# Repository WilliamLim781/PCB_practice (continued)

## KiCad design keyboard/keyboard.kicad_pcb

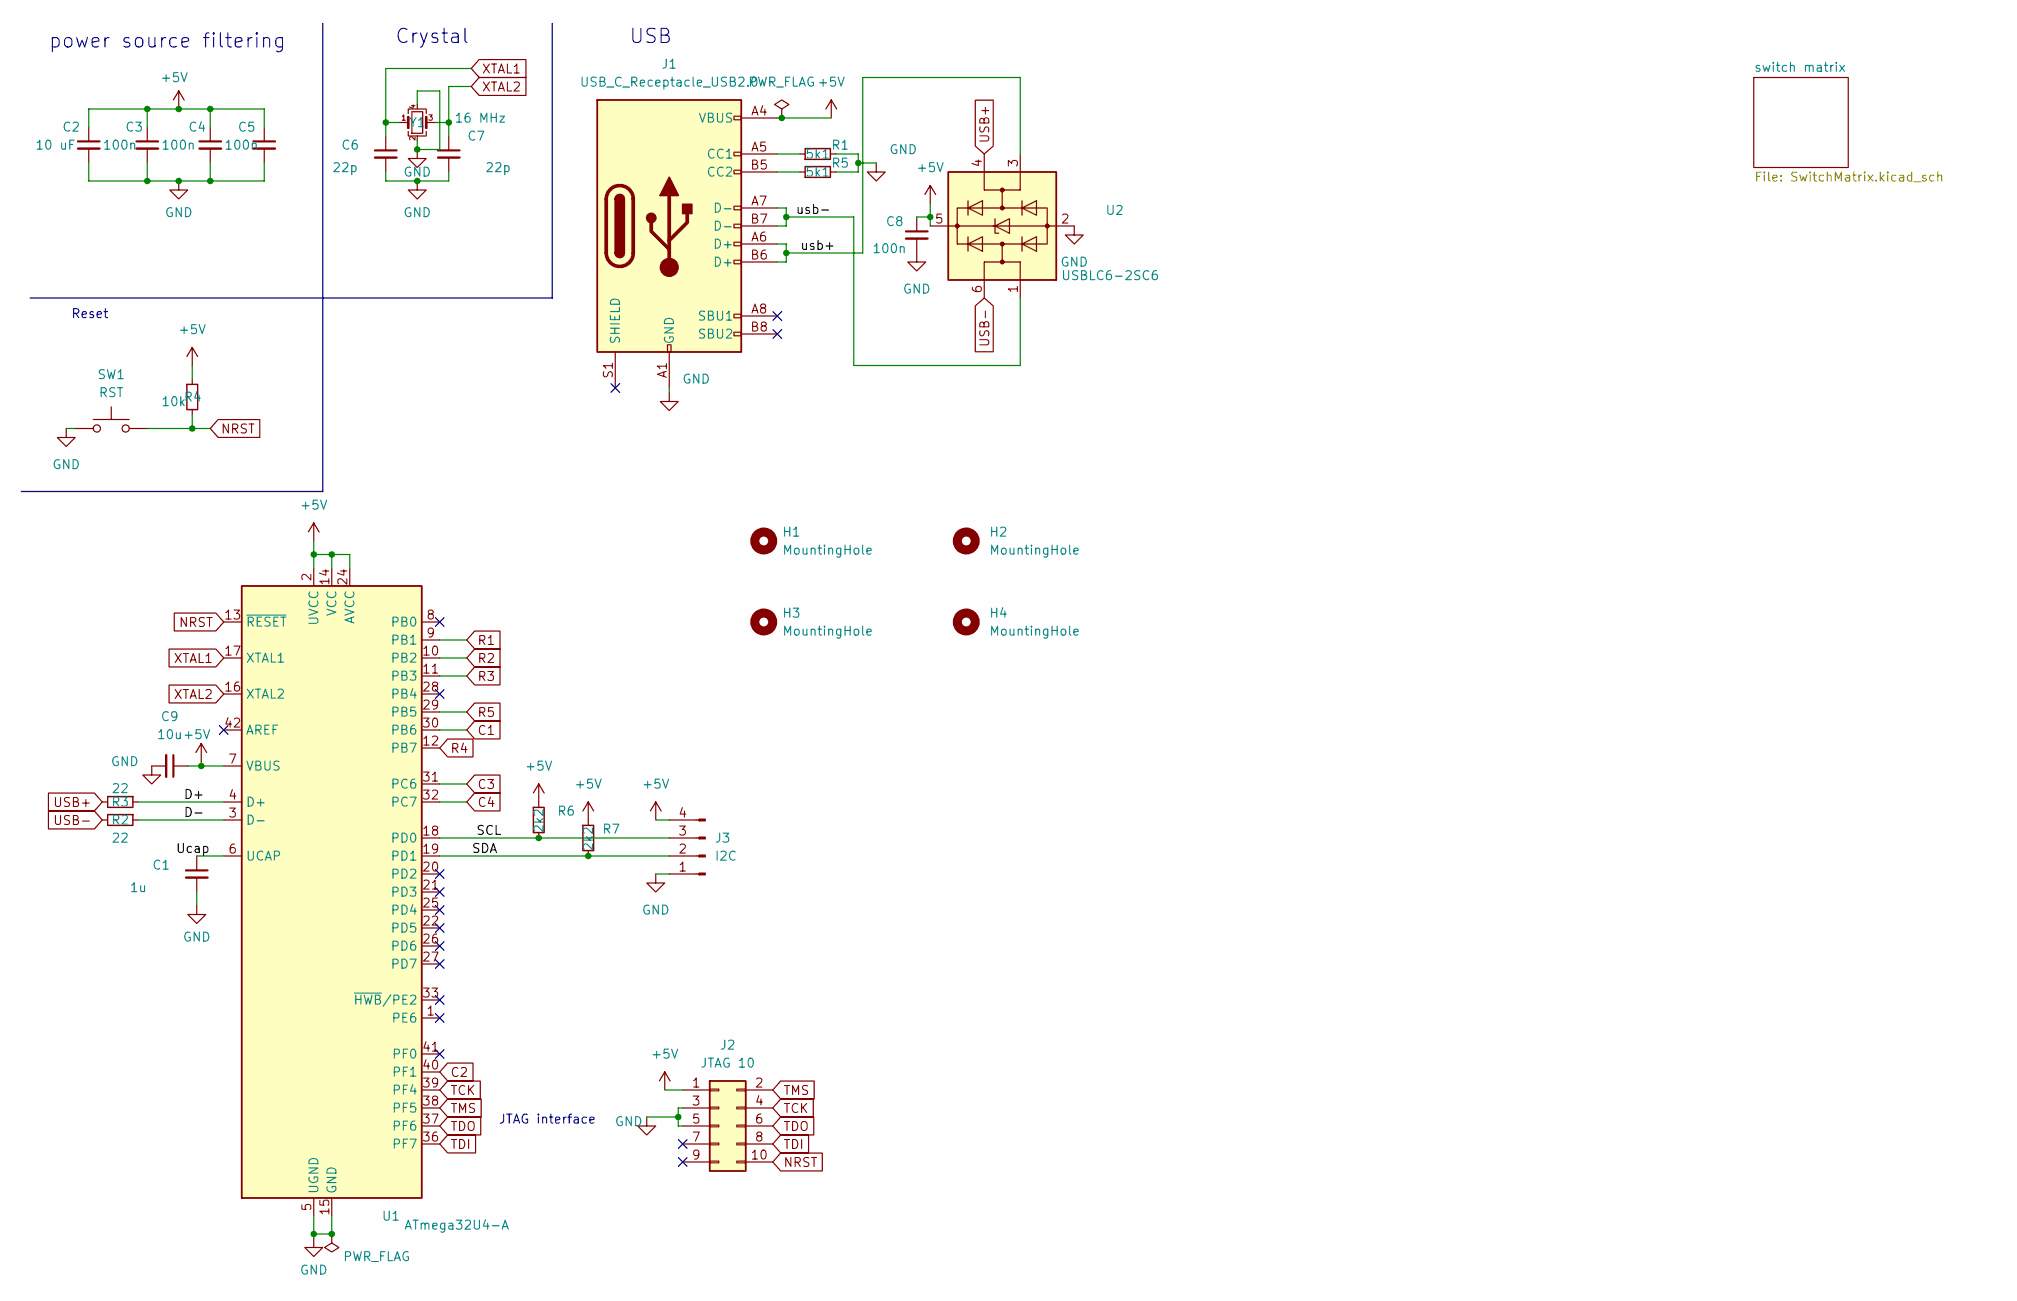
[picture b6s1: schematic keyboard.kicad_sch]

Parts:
C1: 1u; C_0603_1608Metric_Pad1.08x0.95mm_HandSolder
C2: 10 uF; C_0603_1608Metric_Pad1.08x0.95mm_HandSolder
C3, C4, C5, C8: 100n; C_0603_1608Metric_Pad1.08x0.95mm_HandSolder
C6, C7: 22p; C_0603_1608Metric_Pad1.08x0.95mm_HandSolder
C9: 10u; C_0603_1608Metric_Pad1.08x0.95mm_HandSolder
H1, H2, H3, H4: MountingHole; MountingHole_4.3mm_M4
J1: USB_C_Receptacle_USB2.0; USB_C_Receptacle_GCT_USB4105-xx-A_16P_TopMnt_Horizontal
J2: JTAG 10; PinHeader_2x05_P2.54mm_Vertical
J3: I2C; PinHeader_1x04_P2.54mm_Vertical
R1, R5: 5k1; R_0603_1608Metric_Pad0.98x0.95mm_HandSolder
R2, R3: 22; R_0603_1608Metric_Pad0.98x0.95mm_HandSolder
R4: 10k; R_0603_1608Metric_Pad0.98x0.95mm_HandSolder
R6, R7: 2k2; R_0603_1608Metric_Pad0.98x0.95mm_HandSolder
SW1: RST; SW_SPST_PTS645
U1: ATmega32U4-A; TQFP-44_10x10mm_P0.8mm
U2: USBLC6-2SC6; SOT-23-6
Y1: 16 MHz; Crystal_SMD_3225-4Pin_3.2x2.5mm_HandSoldering

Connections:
+5V: C2.1, C3.1, C4.1, C5.1, C8.1, C9.1, J1.A4 (VBUS), J1.A9 (VBUS), J1.B4 (VBUS), J1.B9 (VBUS), J2.1, J3.4, R4.1, R6.1, R7.1, U1.2 (UVCC), U1.7 (VBUS), U1.14 (VCC), U1.24 (AVCC), U1.34 (VCC), U1.44 (AVCC), U2.5 (VBUS)
/D+: R3.1, U1.4 (D+)
/D-: R2.1, U1.3 (D-)
/SCL: J3.3, R6.2, U1.18 (PD0)
/SDA: J3.2, R7.2, U1.19 (PD1)
/Ucap: C1.1, U1.6 (UCAP)
/usb+: J1.A6 (D+), J1.B6 (D+), U2.3 (I/O2)
/usb-: J1.A7 (D-), J1.B7 (D-), U2.1 (I/O1)
C1: U1.30 (PB6); also elsewhere on the board
C2: U1.40 (PF1); also elsewhere on the board
C3: U1.31 (PC6); also elsewhere on the board
C4: U1.32 (PC7); also elsewhere on the board
GND: C1.2, C2.2, C3.2, C4.2, C5.2, C6.2, C7.2, C8.2, C9.2, J1.A1 (GND), J1.A12 (GND), J1.B1 (GND), J1.B12 (GND), J2.3, J2.5, J3.1, R1.2, R5.2, SW1.1, U1.5 (UGND), U1.15 (GND), U1.23 (GND), U1.35 (GND), U1.43 (GND), U2.2 (GND), Y1.2, Y1.4
NRST: J2.10, R4.2, SW1.2, U1.13 (~RESET)
unnamed: J1.A5 (CC1), R1.1
unnamed: J1.B5 (CC2), R5.1
R1: U1.9 (PB1); also elsewhere on the board
R2: U1.10 (PB2); also elsewhere on the board
R3: U1.11 (PB3); also elsewhere on the board
R4: U1.12 (PB7); also elsewhere on the board
R5: U1.29 (PB5); also elsewhere on the board
TCK: J2.4, U1.39 (PF4)
TDI: J2.8, U1.36 (PF7)
TDO: J2.6, U1.37 (PF6)
TMS: J2.2, U1.38 (PF5)
USB+: R3.2, U2.4 (I/O2)
USB-: R2.2, U2.6 (I/O1)
XTAL1: C6.1, U1.17 (XTAL1), Y1.1
XTAL2: C7.1, U1.16 (XTAL2), Y1.3

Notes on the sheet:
Reset
Crystal
JTAG interface
power source filtering
USB

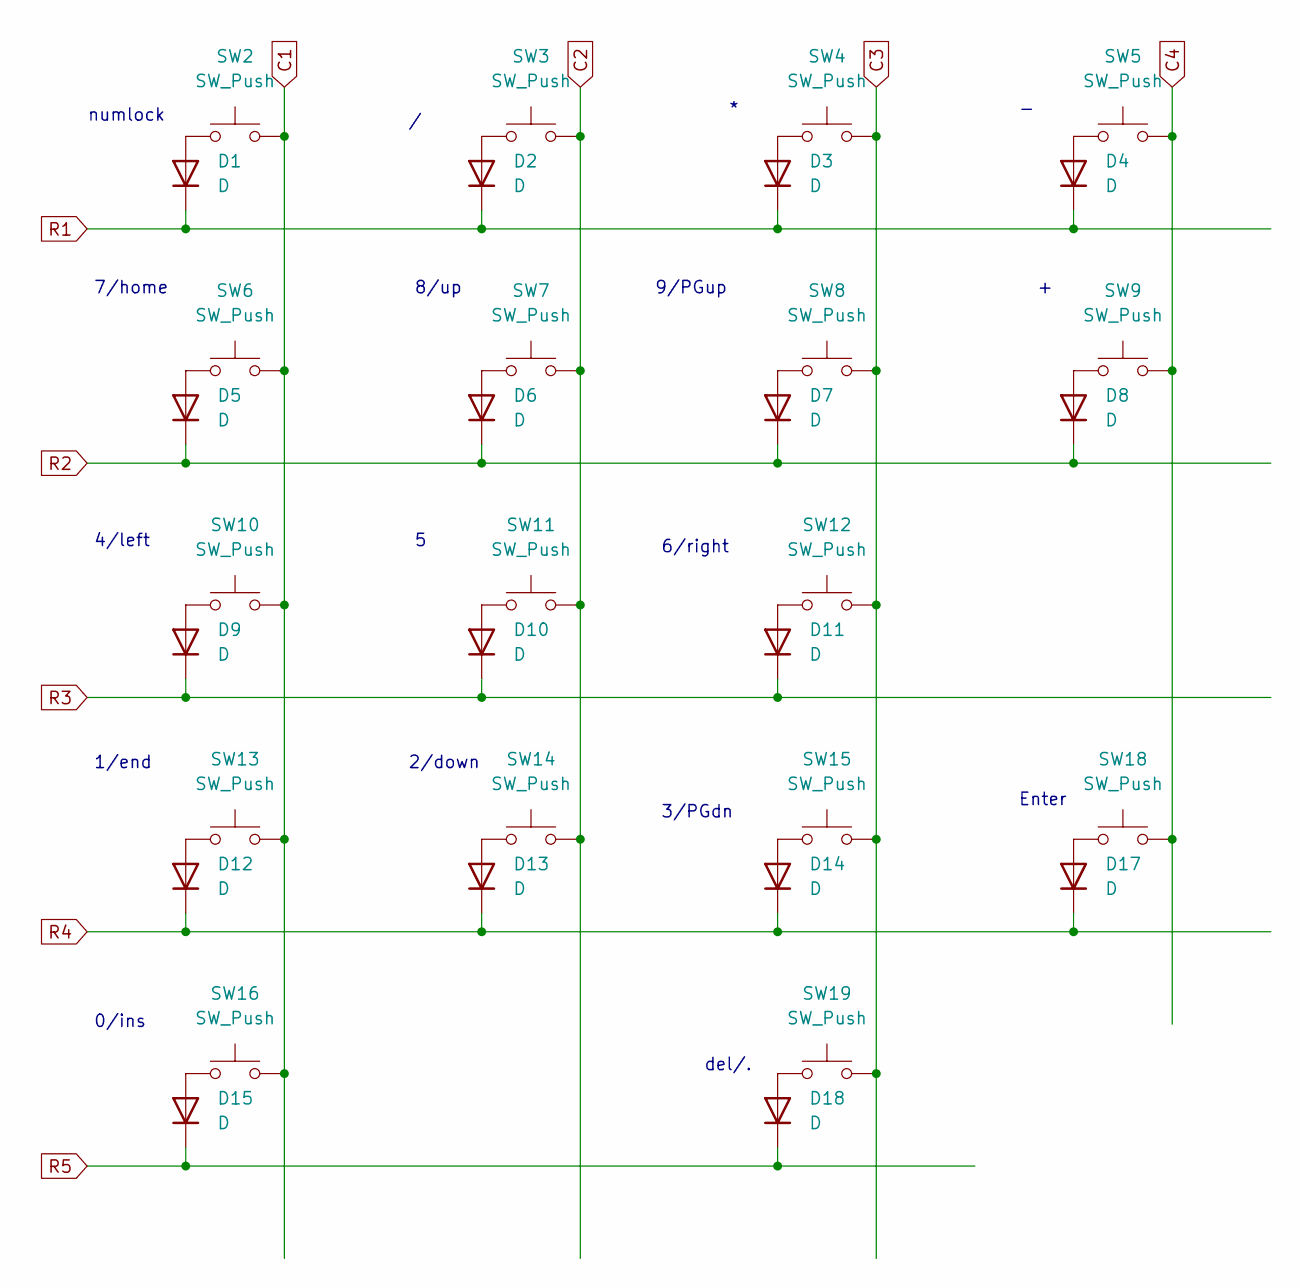
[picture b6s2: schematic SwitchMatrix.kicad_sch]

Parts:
D1, D2, D3, D4, D5, D6, D7, D8, D9, D10, D11, D12, D13, D14, D15, D17, D18: D; D_0603_1608Metric_Pad1.05x0.95mm_HandSolder
SW2, SW3, SW4, SW5, SW6, SW7, SW8, SW10, SW11, SW12, SW13, SW14, SW15, SW19: SW_Push; SW_Hotswap_Kailh_MX_1.00u
SW9, SW18: SW_Push; SW_Hotswap_Kailh_MX_2.00u_90deg
SW16: SW_Push; SW_Hotswap_Kailh_MX_2.00u

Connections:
C1: SW2.2, SW6.2, SW10.2, SW13.2, SW16.2; also elsewhere on the board
C2: SW3.2, SW7.2, SW11.2, SW14.2; also elsewhere on the board
C3: SW4.2, SW8.2, SW12.2, SW15.2, SW19.2; also elsewhere on the board
C4: SW5.2, SW9.2, SW18.2; also elsewhere on the board
unnamed: D1.2 (A), SW2.1
unnamed: D2.2 (A), SW3.1
unnamed: D3.2 (A), SW4.1
unnamed: D4.2 (A), SW5.1
unnamed: D5.2 (A), SW6.1
unnamed: D6.2 (A), SW7.1
unnamed: D7.2 (A), SW8.1
unnamed: D8.2 (A), SW9.1
unnamed: D9.2 (A), SW10.1
unnamed: D10.2 (A), SW11.1
unnamed: D11.2 (A), SW12.1
unnamed: D12.2 (A), SW13.1
unnamed: D13.2 (A), SW14.1
unnamed: D14.2 (A), SW15.1
unnamed: D15.2 (A), SW16.1
unnamed: D17.2 (A), SW18.1
unnamed: D18.2 (A), SW19.1
R1: D1.1 (K), D2.1 (K), D3.1 (K), D4.1 (K); also elsewhere on the board
R2: D5.1 (K), D6.1 (K), D7.1 (K), D8.1 (K); also elsewhere on the board
R3: D9.1 (K), D10.1 (K), D11.1 (K); also elsewhere on the board
R4: D12.1 (K), D13.1 (K), D14.1 (K), D17.1 (K); also elsewhere on the board
R5: D15.1 (K), D18.1 (K); also elsewhere on the board

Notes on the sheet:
9/PGup
Enter
2/down
0/ins
3/PGdn
4/left
7/home
numlock
del/.
8/up
6/right
1/end

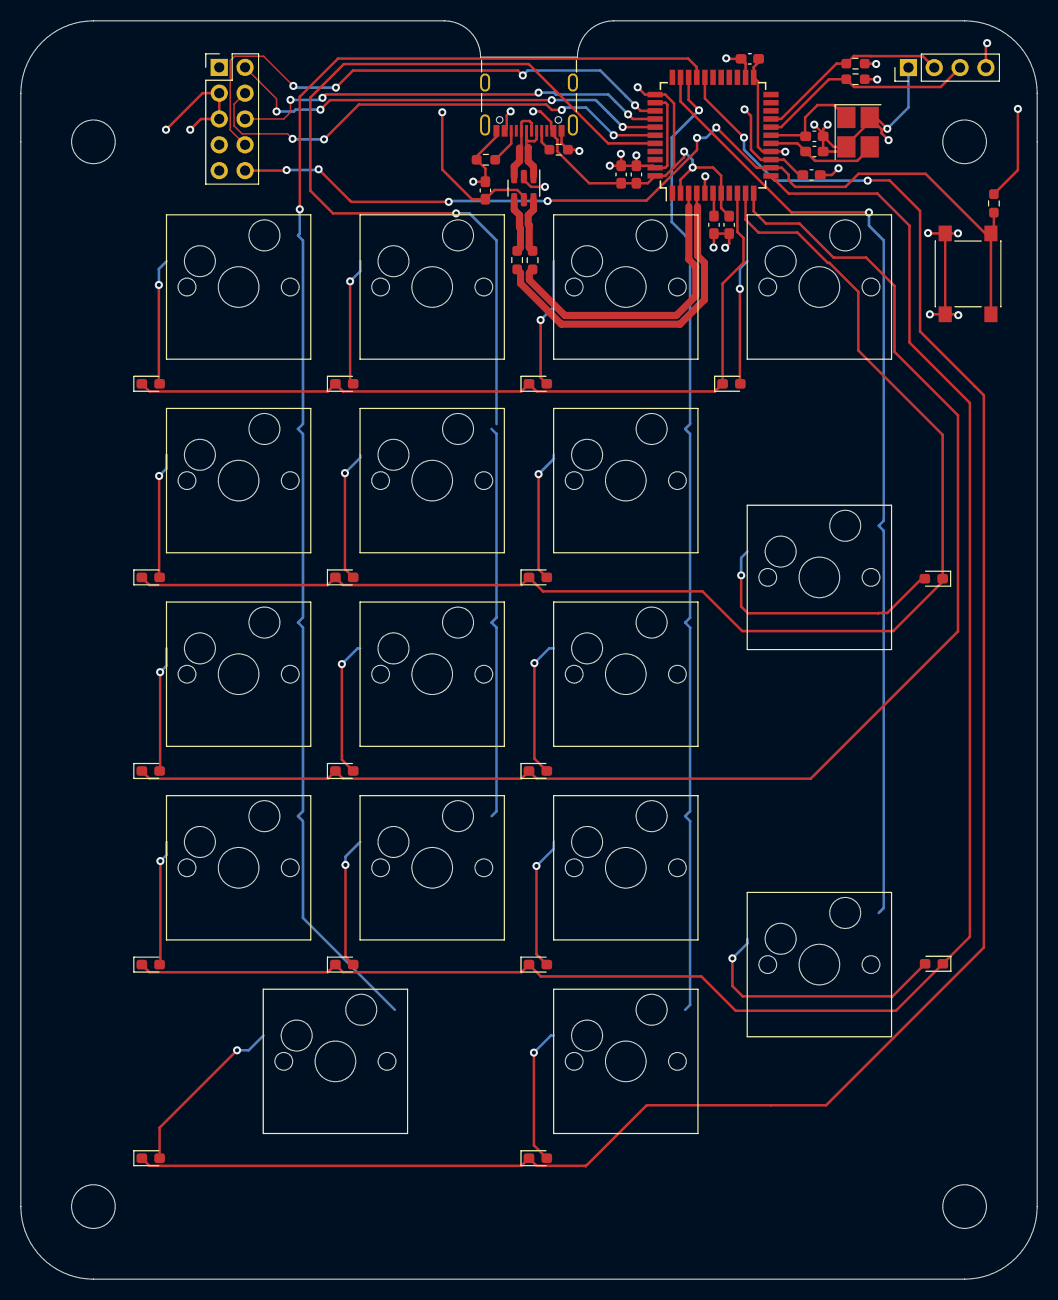
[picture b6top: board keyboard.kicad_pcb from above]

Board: 2 copper layers, 100.0 x 123.8 mm, 61 parts (0 on the bottom side), 46 nets.

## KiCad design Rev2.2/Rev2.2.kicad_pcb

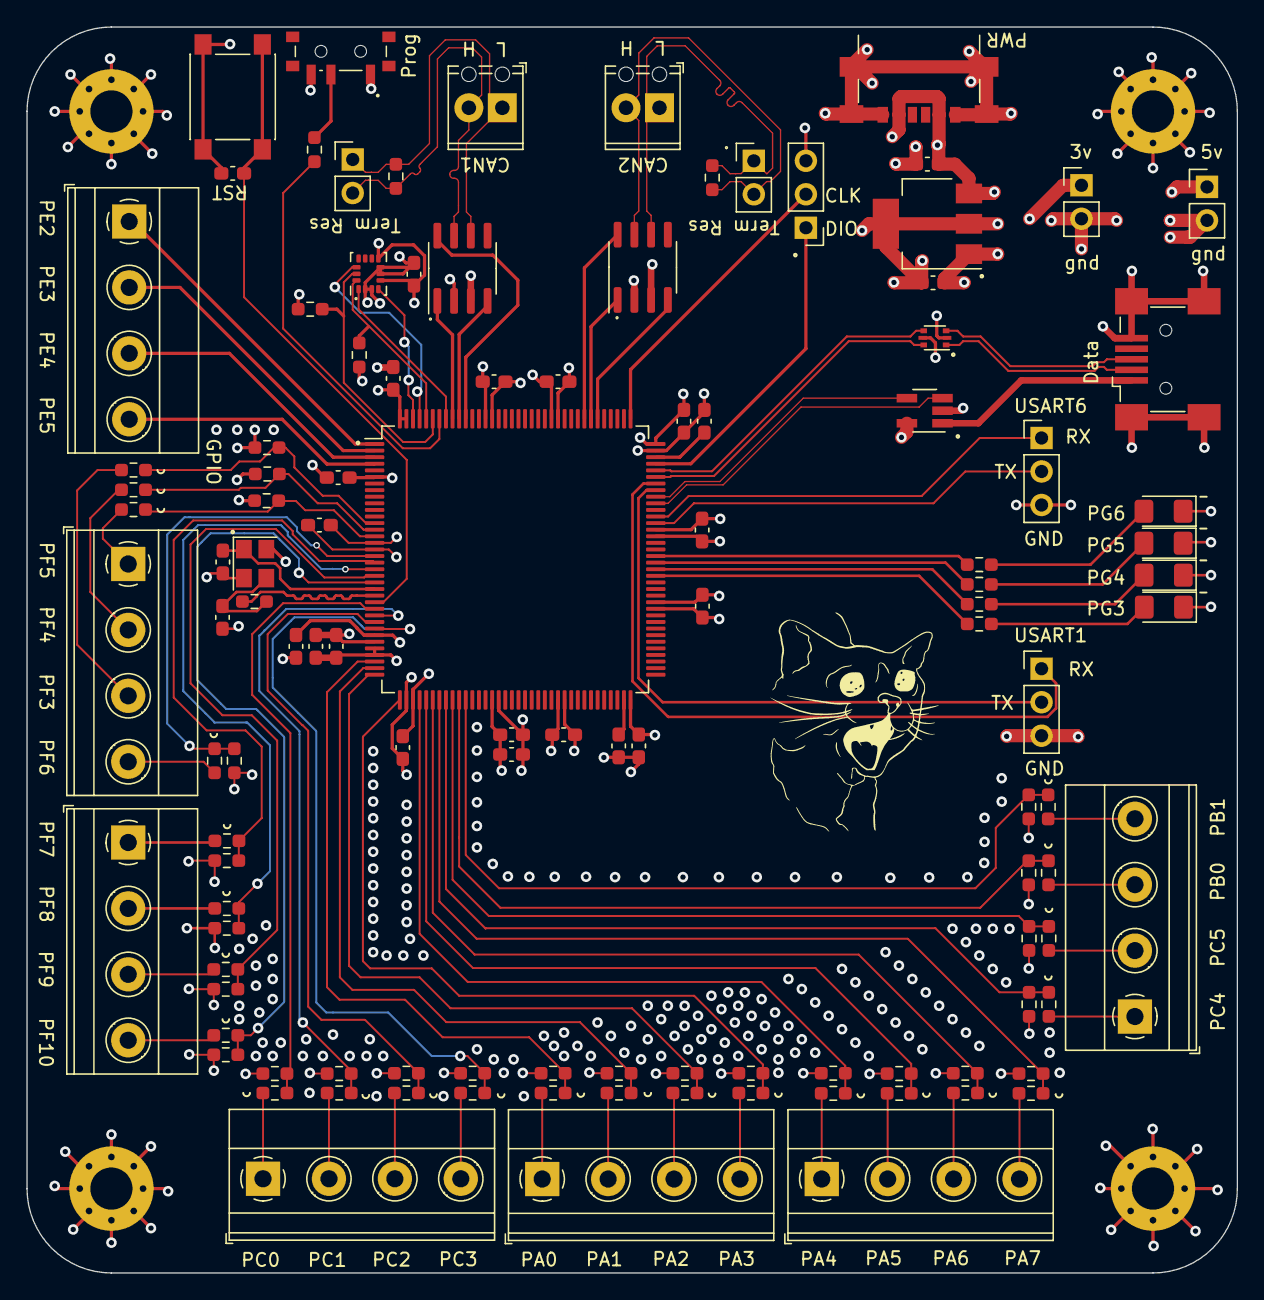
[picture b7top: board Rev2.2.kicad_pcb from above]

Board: 4 copper layers, 91.8 x 94.5 mm, 118 parts (0 on the bottom side), 99 nets.

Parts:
C1, C23, C24, C25, C28, C33, C34, C35, C36, C37, C38, C39, C40, C41, C43, C45: 100n; C_0603_1608Metric_Pad1.08x0.95mm_HandSolder
C26: 10u; C_0603_1608Metric_Pad1.08x0.95mm_HandSolder
C27, C31: 9p; C_0603_1608Metric_Pad1.08x0.95mm_HandSolder
C29, C30: 2.2u; C_0603_1608Metric_Pad1.08x0.95mm_HandSolder
C32: 22u; C_0603_1608Metric_Pad1.08x0.95mm_HandSolder
C42: 4.7u; C_0603_1608Metric_Pad1.08x0.95mm_HandSolder
C44: 1u; C_0603_1608Metric_Pad1.08x0.95mm_HandSolder
D1: LED1; LED_1206_3216Metric_Pad1.42x1.75mm_HandSolder
D2: LED2; LED_1206_3216Metric_Pad1.42x1.75mm_HandSolder
D3: LED3; LED_1206_3216Metric_Pad1.42x1.75mm_HandSolder
D4: LED4; LED_1206_3216Metric_Pad1.42x1.75mm_HandSolder
H1, H2, H3, H4: MountingHole_Pad; MountingHole_3.2mm_M3_Pad_Via
J1, J3: Termination; PinHeader_1x02_P2.54mm_Vertical
J2: CAN2; TerminalBlock_Phoenix_MPT-0,5-2-2.54_1x02_P2.54mm_Horizontal
J4: CAN1; TerminalBlock_Phoenix_MPT-0,5-2-2.54_1x02_P2.54mm_Horizontal
J5: SWD; PinHeader_1x03_P2.54mm_Vertical
J6: USB_OTG; USB_Mini-B_Wuerth_65100516121_Horizontal
J7: GPIO1; TerminalBlock_Phoenix_MKDS-1,5-4_1x04_P5.00mm_Horizontal
J8, J18: AIN4; TerminalBlock_Phoenix_MKDS-1,5-4_1x04_P5.00mm_Horizontal
J9: AIN5; TerminalBlock_Phoenix_MKDS-1,5-4_1x04_P5.00mm_Horizontal
J10: USART1; PinHeader_1x03_P2.54mm_Vertical
J11: 3.3V power breakout; PinHeader_1x02_P2.54mm_Vertical
J12: 5V power breakout; PinHeader_1x02_P2.54mm_Vertical
J13: AIN1; TerminalBlock_Phoenix_MKDS-1,5-4_1x04_P5.00mm_Horizontal
J14: USB C PWR; USB_C_Receptacle_GCT_USB4135-GF-A_6P_TopMnt_Horizontal
J15: USART6; PinHeader_1x03_P2.54mm_Vertical
J16: AIN2; TerminalBlock_Phoenix_MKDS-1,5-4_1x04_P5.00mm_Horizontal
J17: AIN3; TerminalBlock_Phoenix_MKDS-1,5-4_1x04_P5.00mm_Horizontal
R1, R2: 120; R_0603_1608Metric_Pad0.98x0.95mm_HandSolder
R3, R5, R6, R7, R8, R9, R10, R11, R12, R13, R14, R15, R16, R25, R26, R27, R28, R37, R38, R39, R40, R41, R42, R43, R44: 10k; R_0603_1608Metric_Pad0.98x0.95mm_HandSolder
R4: 0; R_0603_1608Metric_Pad0.98x0.95mm_HandSolder
R17, R18, R19, R20, R21, R22, R23, R24, R29, R30, R31, R32, R33, R34, R35, R36, R47, R48, R49, R50, R51, R52, R53, R54: 20k; R_0603_1608Metric_Pad0.98x0.95mm_HandSolder
R45, R46: 2k2; R_0603_1608Metric_Pad0.98x0.95mm_HandSolder
R55, R56, R57, R58: 100; R_0603_1608Metric_Pad0.98x0.95mm_HandSolder
SW3: SW_SPDT; SW_SPDT_PCM12
SW5: SW_Push; SW_SPST_PTS645
U1: STM32F429ZITx; LQFP-144_20x20mm_P0.5mm
U2, U4: TJA1051T; SOIC-8_3.9x4.9mm_P1.27mm
U3: AMS1117-3.3; SOT-223-3_TabPin2
U5: LGA-14_3x2.5mm_P0.5mm_LayoutBorder3x4y
U9: STMPS2151STR(Current protection); SOT-23-5_HandSoldering
U10: USBLC6-2P6(ESD protection); SOT-666
Y2: 16MHz; Crystal_SMD_3225-4Pin_3.2x2.5mm

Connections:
+3.3V: C1.1, C23.1, C24.1, C25.1, C28.1, C32.1, C33.1, C34.1, C35.1, C36.1, C37.1, C38.1, C39.1, C40.1, C41.1, C42.1, C43.1, C44.1, J11.1, R45.1, R46.1, SW3.1 (A), U1.6 (VBAT), U1.17 (VDD), U1.30 (VDD), U1.32 (VREF+), U1.33 (VDDA), U1.39 (VDD), U1.52 (VDD), U1.62 (VDD), U1.72 (VDD), U1.84 (VDD), U1.95 (VDD), U1.108 (VDD), U1.121 (VDD), U1.131 (VDD), U1.143 (PDR_ON), U1.144 (VDD), U3.2 (VO), U5.5 (VDDIO), U5.8 (VDD)
+5V: C26.1, J12.1, J14.A9 (VBUS), J14.B9 (VBUS), U2.3 (VCC), U3.3 (VI), U4.3 (VCC), U9.5 (VIN), U10.5 (VBUS)
/CAN1+: J3.2, J4.2, R2.2, U4.7 (CANH)
/CAN1-: J3.1, J4.1, R2.1, U4.6 (CANL)
/CAN2+: J1.2, J2.2, R1.2, U2.7 (CANH)
/CAN2-: J1.1, J2.1, R1.1, U2.6 (CANL)
/USB wiring/VBUS1: J6.1 (VBUS), U9.1 (OUT)
A1: R25.2, R33.1, U1.13 (PF3)
A2: R26.2, R34.1, U1.14 (PF4)
A3: R27.2, R35.1, U1.15 (PF5)
A4: R28.2, R36.1, U1.18 (PF6)
A5: R5.2, R29.1, U1.19 (PF7)
A6: R6.2, R30.1, U1.20 (PF8)
A7: R7.2, R31.1, U1.21 (PF9)
A8: R8.2, R32.1, U1.22 (PF10)
A9: R9.2, R17.1, U1.26 (PC0)
A10: R10.2, R18.1, U1.27 (PC1)
A11: R11.2, R19.1, U1.28 (PC2)
A12: R12.2, R20.1, U1.29 (PC3)
A13: R13.2, R21.1, U1.34 (PA0)
A14: R14.2, R22.1, U1.35 (PA1)
A15: R15.2, R23.1, U1.36 (PA2)
A16: R16.2, R24.1, U1.37 (PA3)
A17: R37.2, R47.1, U1.40 (PA4)
A18: R38.2, R48.1, U1.41 (PA5)
A19: R39.2, R49.1, U1.42 (PA6)
A20: R40.2, R50.1, U1.43 (PA7)
A21: R41.2, R51.1, U1.44 (PC4)
A22: R42.2, R52.1, U1.45 (PC5)
A23: R43.2, R53.1, U1.46 (PB0)
A24: R44.2, R54.1, U1.47 (PB1)
BOOT0: R3.1, U1.138 (BOOT0)
CAN1_RX: U1.114 (PD0), U4.4 (RXD)
CAN1_TX: U1.115 (PD1), U4.1 (TXD)
CAN2_RX: U1.135 (PB5), U2.4 (RXD)
CAN2_TX: U1.136 (PB6), U2.1 (TXD)
GND: C1.2, C23.2, C24.2, C25.2, C26.2, C27.2, C28.2, C29.2, C30.2, C31.2, C32.2, C33.2, C34.2, C35.2, C36.2, C37.2, C38.2, C39.2, C40.2, C41.2, C42.2, C43.2, C44.2, C45.2, D1.1 (K), D2.1 (K), D3.1 (K), D4.1 (K), H1.1, H2.1, H3.1, H4.1, J5.3, J6.5 (GND), J6.6 (Shield), J10.3, J11.2, J12.2, J14.A12 (GND), J14.B12 (GND), J14.S1 (SHIELD), J15.3, R17.2, R18.2, R19.2, R20.2, R21.2, R22.2, R23.2, R24.2, R29.2, R30.2, R31.2, R32.2, R33.2, R34.2, R35.2, R36.2, R47.2, R48.2, R49.2, R50.2, R51.2, R52.2, R53.2, R54.2, SW3.3 (C), SW5.1, U1.16 (VSS), U1.31 (VSSA), U1.38 (VSS), U1.51 (VSS), U1.61 (VSS), U1.83 (VSS), U1.94 (VSS), U1.107 (VSS), U1.120 (VSS), U1.130 (VSS), U2.2 (GND), U3.1 (GND), U4.2 (GND), U5.2 (SDX), U5.3 (SCX), U5.6 (GND), U5.7 (GND), U9.2 (GND), U10.2 (GND), Y2.2, Y2.4
GPIO1: J7.1, U1.1 (PE2)
GPIO2: J7.2, U1.2 (PE3)
GPIO3: J7.3, U1.3 (PE4)
GPIO4: J7.4, U1.4 (PE5)
HSE_IN: C27.1, U1.23 (PH0), Y2.1
HSE_OUT: R4.1, U1.24 (PH1)
LSM6DSOX_CS: U1.141 (PE0), U5.12 (CS)
LSM6DSOX_SCL: R45.2, U1.139 (PB8), U5.13 (SCL)
LSM6DSOX_SDA: R46.2, U1.140 (PB9), U5.14 (SDA)
LSM6DSOX_SDO: U1.137 (PB7), U5.1 (SD0)
LSM6DSOX_int1: U1.142 (PE1), U5.4 (INT1)
NRST: C45.1, SW5.2, U1.25 (NRST)
unnamed: C31.1, R4.2, Y2.3
unnamed: D1.2 (A), R55.1
unnamed: D2.2 (A), R56.1
unnamed: D3.2 (A), R57.1
unnamed: D4.2 (A), R58.1
unnamed: J8.1, R41.1
unnamed: J8.2, R42.1
unnamed: J8.3, R43.1
unnamed: J8.4, R44.1
unnamed: J9.1, R37.1
unnamed: J9.2, R38.1
unnamed: J9.3, R39.1
unnamed: J9.4, R40.1
unnamed: J13.1, R27.1
unnamed: J13.2, R26.1
unnamed: J13.3, R25.1
unnamed: J13.4, R28.1
unnamed: J16.1, R5.1
unnamed: J16.2, R6.1
unnamed: J16.3, R7.1
unnamed: J16.4, R8.1
unnamed: J17.1, R13.1
unnamed: J17.2, R14.1
unnamed: J17.3, R15.1
unnamed: J17.4, R16.1
unnamed: J18.1, R9.1
unnamed: J18.2, R10.1
unnamed: J18.3, R11.1
unnamed: J18.4, R12.1
unnamed: R3.2, SW3.2 (B)
unnamed: R55.2, U1.88 (PG3)
unnamed: R56.2, U1.89 (PG4)
unnamed: R57.2, U1.90 (PG5)
unnamed: R58.2, U1.91 (PG6)
STMPS2151STR_EN: U1.100 (PA8), U9.4 (EN)
STMPS2151STR_FAULT: U1.99 (PC9), U9.3 (FAULT)
SYS_JTCK_SWCLK: J5.2, U1.109 (PA14)
SYS_JTMS_SWDIO: J5.1, U1.105 (PA13)
Silent_Mode1: U1.116 (PD2), U4.8 (S)
Silent_Mode2: U1.134 (PB4), U2.8 (S)
USART1_RX: J10.1, U1.102 (PA10)
USART1_TX: J10.2, U1.101 (PA9)
USART6_RX: J15.1, U1.97 (PC7)
USART6_TX: J15.2, U1.96 (PC6)
USBData->ESD+: J6.3 (D+), U10.3 (I/O2)
USBData->ESD-: J6.2 (D-), U10.1 (I/O1)
USB_DATA+: U1.104 (PA12), U10.4 (I/O2)
USB_DATA-: U1.103 (PA11), U10.6 (I/O1)
VCAP_1: C29.1, U1.71 (VCAP_1)
VCAP_2: C30.1, U1.106 (VCAP_2)

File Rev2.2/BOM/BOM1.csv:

Designator,Comment,Footprint,JLCpart#
"C1, C2, C5, C8, C11, C12, C23, C24, C25, C28, C33, C34, C35, C36, C37, C38, C39, C40, C41, C43, C45",100n,Capacitor_SMD:C_0603_1608Metric_Pad1.08x0.95mm_HandSolder,C14663
C26,10u,Capacitor_SMD:C_0603_1608Metric_Pad1.08x0.95mm_HandSolder,C96446
"C27, C31",9p,Capacitor_SMD:C_0603_1608Metric_Pad1.08x0.95mm_HandSolder,C282076
"C29, C30",2.2u,Capacitor_SMD:C_0603_1608Metric_Pad1.08x0.95mm_HandSolder,C23630
C32,22u,Capacitor_SMD:C_0603_1608Metric_Pad1.08x0.95mm_HandSolder,C59461
C42,4.7u,Capacitor_SMD:C_0603_1608Metric_Pad1.08x0.95mm_HandSolder,C19666
C44,1u,Capacitor_SMD:C_0603_1608Metric_Pad1.08x0.95mm_HandSolder,C15849
D1,LED1,LED_SMD:LED_1206_3216Metric_Pad1.42x1.75mm_HandSolder,C712085
D2,LED2,LED_SMD:LED_1206_3216Metric_Pad1.42x1.75mm_HandSolder,C712085
D3,LED3,LED_SMD:LED_1206_3216Metric_Pad1.42x1.75mm_HandSolder,C712085
D4,LED4,LED_SMD:LED_1206_3216Metric_Pad1.42x1.75mm_HandSolder,C712085
H1-H4,MountingHole_Pad,MountingHole:MountingHole_3.2mm_M3_Pad_Via,
"J1, J3",Termination ,Connector_PinHeader_2.54mm:PinHeader_1x02_P2.54mm_Vertical,
J2,CAN2,"TerminalBlock_Phoenix:TerminalBlock_Phoenix_MPT-0,5-2-2.54_1x02_P2.54mm_Horizontal",
J4,CAN1,"TerminalBlock_Phoenix:TerminalBlock_Phoenix_MPT-0,5-2-2.54_1x02_P2.54mm_Horizontal",
J5,SWD,Connector_PinHeader_2.54mm:PinHeader_1x03_P2.54mm_Vertical,
J6,USB_OTG,Connector_USB:USB_Mini-B_Wuerth_65100516121_Horizontal,
J7,GPIO1,"TerminalBlock_Phoenix:TerminalBlock_Phoenix_MKDS-1,5-4_1x04_P5.00mm_Horizontal",
"J8, J18",AIN4,"TerminalBlock_Phoenix:TerminalBlock_Phoenix_MKDS-1,5-4_1x04_P5.00mm_Horizontal",
J9,AIN5,"TerminalBlock_Phoenix:TerminalBlock_Phoenix_MKDS-1,5-4_1x04_P5.00mm_Horizontal",
J10,USART1,Connector_PinHeader_2.54mm:PinHeader_1x03_P2.54mm_Vertical,
J11,3.3V power breakout,Connector_PinHeader_2.54mm:PinHeader_1x02_P2.54mm_Vertical,
J12,5V power breakout,Connector_PinHeader_2.54mm:PinHeader_1x02_P2.54mm_Vertical,
J13,AIN1,"TerminalBlock_Phoenix:TerminalBlock_Phoenix_MKDS-1,5-4_1x04_P5.00mm_Horizontal",
J14,USB C PWR,Connector_USB:USB_C_Receptacle_GCT_USB4135-GF-A_6P_TopMnt_Horizontal,
J15,USART6,Connector_PinHeader_2.54mm:PinHeader_1x03_P2.54mm_Vertical,
J16,AIN2,"TerminalBlock_Phoenix:TerminalBlock_Phoenix_MKDS-1,5-4_1x04_P5.00mm_Horizontal",
J17,AIN3,"TerminalBlock_Phoenix:TerminalBlock_Phoenix_MKDS-1,5-4_1x04_P5.00mm_Horizontal",
"R1, R2",120,Resistor_SMD:R_0603_1608Metric_Pad0.98x0.95mm_HandSolder,C22787
"R3, R5,R6,R7,R8,R9,R10,R11,R12,R13,R14,R15,R16, R25,R26,R27,R28, R37,R38,R39,R40,R41,R42,R43,R44",10k,Resistor_SMD:R_0603_1608Metric_Pad0.98x0.95mm_HandSolder,C25804
R4,0,Resistor_SMD:R_0603_1608Metric_Pad0.98x0.95mm_HandSolder,C21189
"R17,R18,R19,R20,R21,R23,R24, R29,R30,R31,R32,R33,R34,R35,R36, R47,R48,R49,R50,R51,R52,R53,R54",20k,Resistor_SMD:R_0603_1608Metric_Pad0.98x0.95mm_HandSolder,C4184
"R45, R46",2k2,Resistor_SMD:R_0603_1608Metric_Pad0.98x0.95mm_HandSolder,C4190
"R55,R56,R57,R58",100,Resistor_SMD:R_0603_1608Metric_Pad0.98x0.95mm_HandSolder,C22775
SW3,SW_SPDT,Button_Switch_SMD:SW_SPDT_PCM12,C221841
SW5,SW_Push,Button_Switch_SMD:SW_SPST_PTS645,
U1,STM32F429ZITx,Package_QFP:LQFP-144_20x20mm_P0.5mm,C84808
"U2, U4",TJA1051T,Package_SO:SOIC-8_3.9x4.9mm_P1.27mm,C7432801
U3,AMS1117-3.3,Package_TO_SOT_SMD:SOT-223-3_TabPin2,C2891839
U5,~,Package_LGA:LGA-14_3x2.5mm_P0.5mm_LayoutBorder3x4y,C481766
U9,STMPS2151STR(Current protection),Package_TO_SOT_SMD:SOT-23-5_HandSoldering,C135998
U10,USBLC6-2P6(ESD protection),Package_TO_SOT_SMD:SOT-666,C2827693
Y2,16MHz,Crystal:Crystal_SMD_3225-4Pin_3.2x2.5mm,C129740

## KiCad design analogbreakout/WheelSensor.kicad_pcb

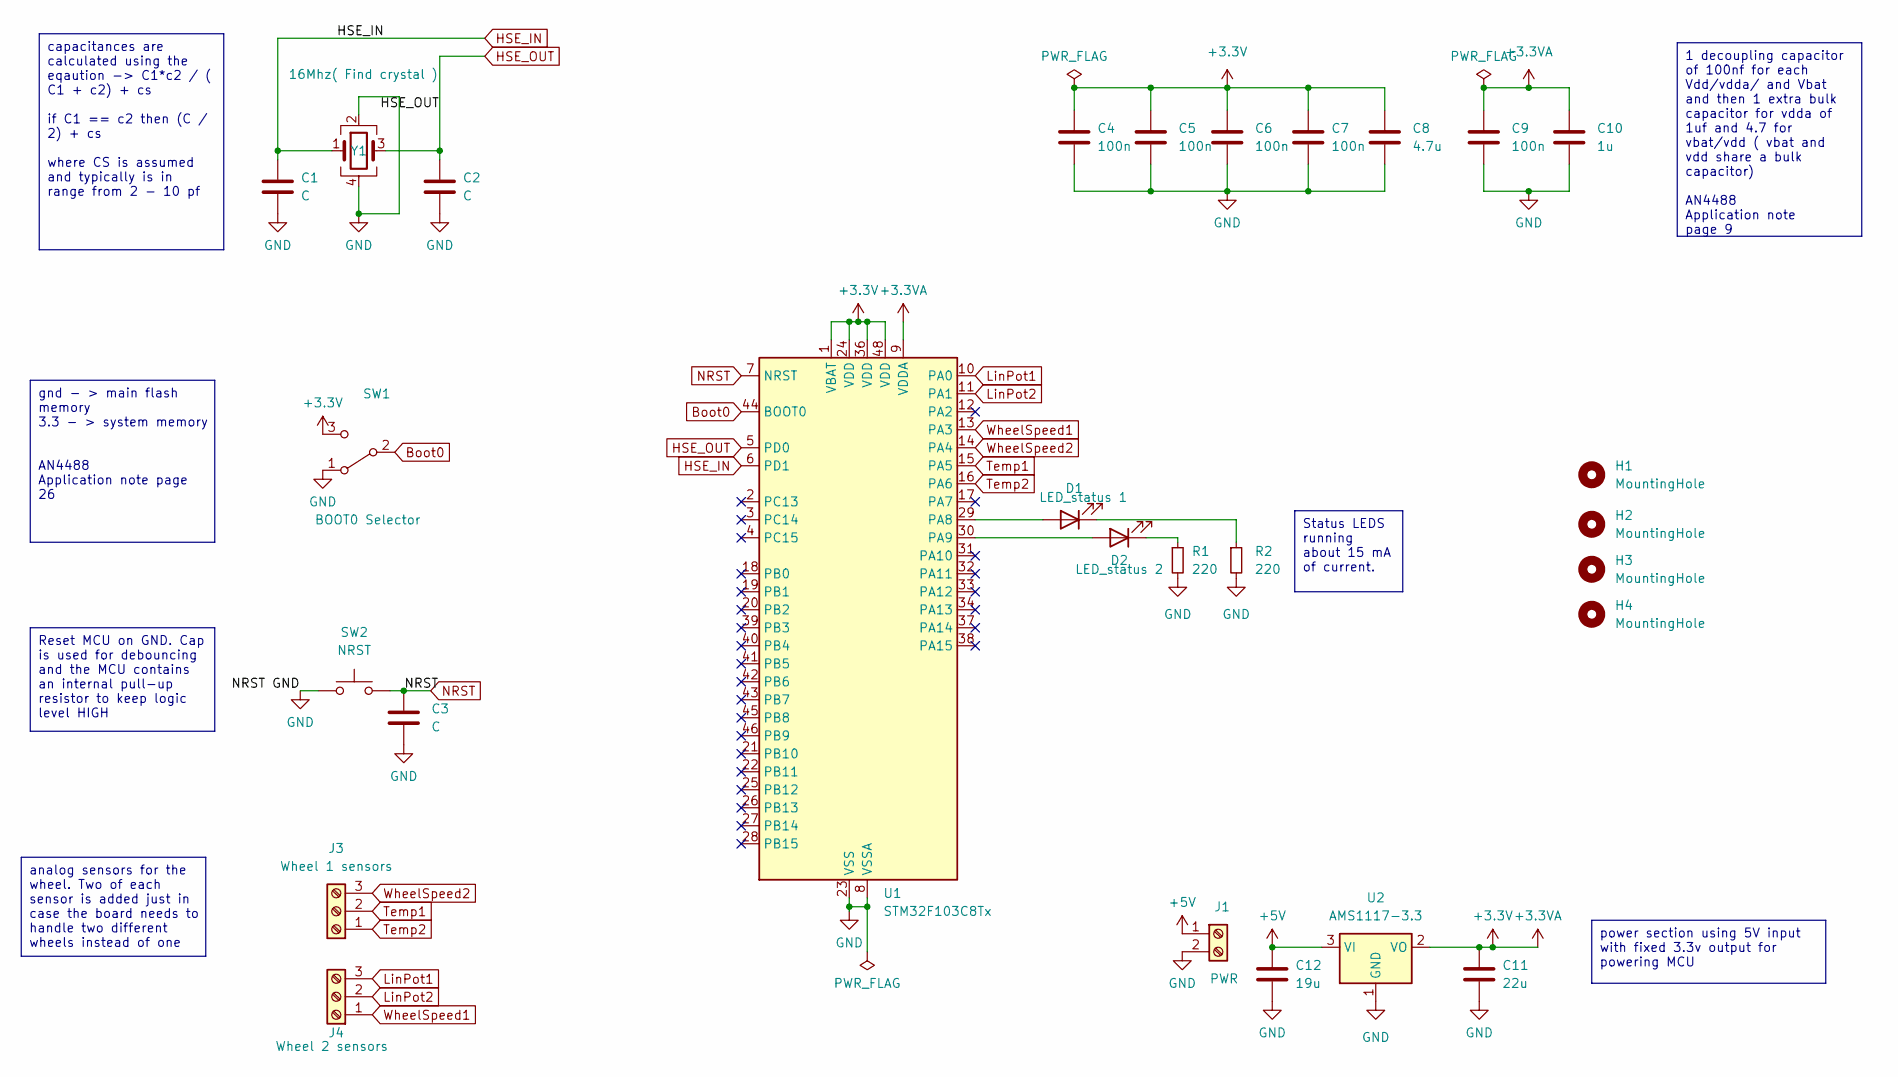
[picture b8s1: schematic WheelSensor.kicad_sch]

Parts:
C1, C2, C3: C; C_0805_2012Metric_Pad1.18x1.45mm_HandSolder
C4, C5, C6, C7, C9: 100n; C_0805_2012Metric_Pad1.18x1.45mm_HandSolder
C8: 4.7u; C_0805_2012Metric_Pad1.18x1.45mm_HandSolder
C10: 1u; C_0805_2012Metric_Pad1.18x1.45mm_HandSolder
C11: 22u; C_0805_2012Metric_Pad1.18x1.45mm_HandSolder
C12: 19u; C_0805_2012Metric_Pad1.18x1.45mm_HandSolder
D1: LED_status 1; LED_1206_3216Metric_Pad1.42x1.75mm_HandSolder
D2: LED_status 2; LED_1206_3216Metric_Pad1.42x1.75mm_HandSolder
H1, H2, H3, H4: MountingHole; MountingHole_3.2mm_M3_Pad_Via
J1: PWR; TerminalBlock_Phoenix_MKDS-1,5-2_1x02_P5.00mm_Horizontal
J3: Wheel 1 sensors; TerminalBlock_Phoenix_MKDS-1,5-3_1x03_P5.00mm_Horizontal
J4: Wheel 2 sensors; TerminalBlock_Phoenix_MKDS-1,5-3_1x03_P5.00mm_Horizontal
R1, R2: 220; R_0805_2012Metric_Pad1.20x1.40mm_HandSolder
SW1: BOOT0 Selector; SW_SPDT_PCM12
SW2: NRST; SW_Push_1P1T_NO_6x6mm_H9.5mm
U1: STM32F103C8Tx; LQFP-48_7x7mm_P0.5mm
U2: AMS1117-3.3; SOT-223-3_TabPin2
Y1: 16Mhz( Find crystal ); Oscillator_SMD_Abracon_ASE-4Pin_3.2x2.5mm_HandSoldering

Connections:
+3.3V: C4.1, C5.1, C6.1, C7.1, C8.1, C9.1, C10.1, C11.1, SW1.3 (C), U1.1 (VBAT), U1.9 (VDDA), U1.24 (VDD), U1.36 (VDD), U1.48 (VDD), U2.2 (VO)
+5V: C12.1, J1.1, U2.3 (VI)
Boot0: SW1.2 (B), U1.44 (BOOT0)
GND: C1.2, C2.2, C3.2, C4.2, C5.2, C6.2, C7.2, C8.2, C9.2, C10.2, C11.2, C12.2, J1.2, R1.2, R2.2, SW1.1 (A), SW2.1, U1.8 (VSSA), U1.23 (VSS), U1.35 (VSS), U1.47 (VSS), U2.1 (GND), Y1.2, Y1.4
HSE_IN: C1.1, U1.6 (PD1), Y1.1
HSE_OUT: C2.1, U1.5 (PD0), Y1.3
LinPot1: J4.3, U1.10 (PA0)
LinPot2: J4.2, U1.11 (PA1)
NRST: C3.1, SW2.2, U1.7 (NRST)
unnamed: D1.2 (A), U1.29 (PA8)
unnamed: D1.1 (K), R2.1
unnamed: D2.2 (A), U1.30 (PA9)
unnamed: D2.1 (K), R1.1
Temp1: J3.2, U1.15 (PA5)
Temp2: J3.1, U1.16 (PA6)
WheelSpeed1: J4.1, U1.13 (PA3)
WheelSpeed2: J3.3, U1.14 (PA4)

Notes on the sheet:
power section using 5V input with fixed 3.3v output for powering MCU
analog sensors for the wheel. Two of each sensor is added just in case the board needs to handle two different wheels instead of one
Reset MCU on GND. Cap is used for debouncing and the MCU contains an internal pull-up resistor to keep logic level HIGH
gnd - > main flash memory 3.3 - > system memory AN4488 Application note page 26
Status LEDS running about 15 mA of current.
1 decoupling capacitor of 100nf for each Vdd/vdda/ and Vbat and then 1 extra bulk capacitor for vdda of 1uf and 4.7 for vbat/vdd ( vbat and vdd share a bulk capacitor) AN4488 Application note page 9
capacitances are calculated using the eqaution -> C1*c2 / ( C1 + c2) + cs if C1 == c2 then (C / 2) + cs where CS is assumed and typically is in range from 2 - 10 pf

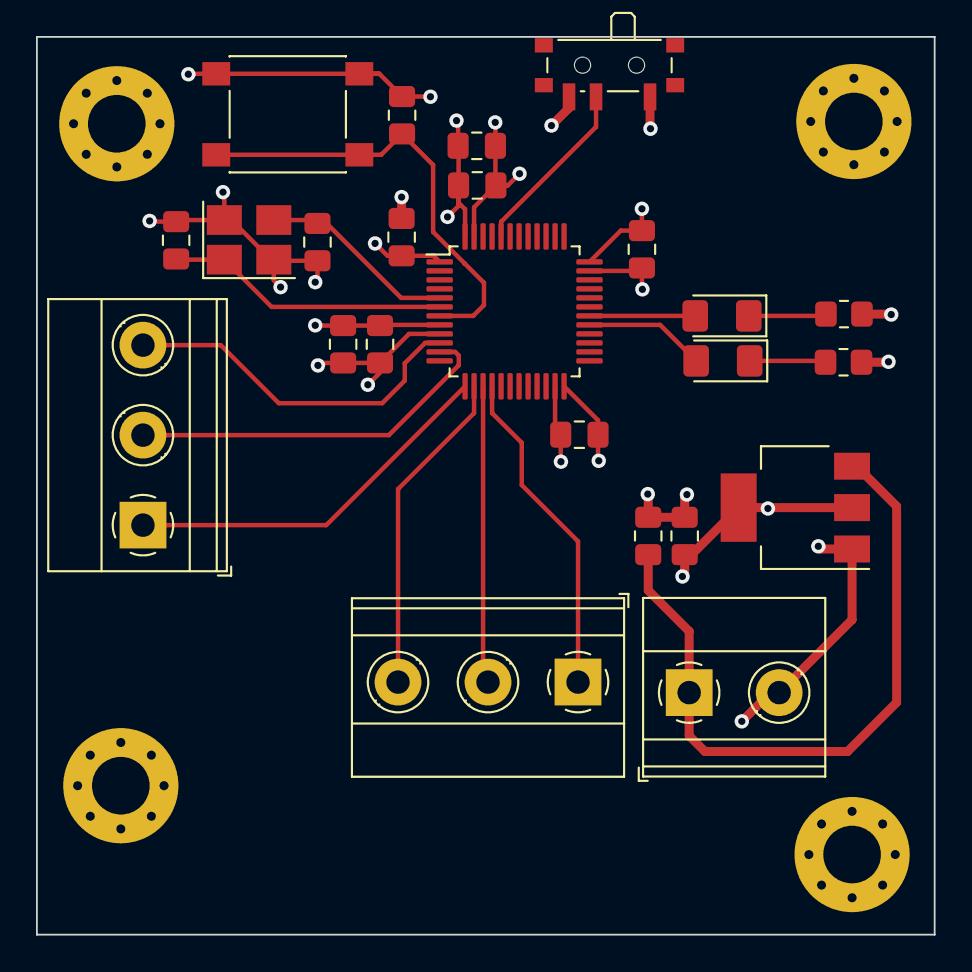
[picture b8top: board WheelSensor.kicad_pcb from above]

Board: 4 copper layers, 49.9 x 49.9 mm, 28 parts (0 on the bottom side), 17 nets.
